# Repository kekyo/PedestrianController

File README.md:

# American pedestrian signal controller on ESP8266

## What's this?

* It's pedestrian signal controller running on ESP8266 (aka ESP-WROOM-02).
* I made custom schematic and artwork from scratch.
  * Use EAGLE 8
* I wrote sequencer code by C++ on ESP8266-Arduino IDE.

### Video

* We record our discussion into YouTube: [Fun with Pedestrian Signal (In japanese)](https://youtu.be/vJiQ18ymqcs)

### NT NAGOYA 2018 conference (2018/10/6)

* We did public and demonstration the MatrixSignalController.
  * It uses with [the ExtremeFeedbackDevice's signal box.](https://github.com/kekyo/ExtremeFeedbackDevice)
  * The three boxes chatting with independent WiFi network, we use http api server and client library.
  * See [the "MatrixSignalController" folder](https://github.com/kekyo/PedestrianController/tree/master/MatrixSignalController) at repository.

## Features

* Basic sequence for american pedestrian signal standard (3 wired control).
* Scheduled time control between signal-on hour and signal-off hour.
* Battery-backuped RTC using scheduler.
* Auto synchronize NTP server with your WiFi AP.

## Schematic and artwork

* I ordered PCB to [Fusion PCB](https://www.seeedstudio.com/fusion_pcb.html) and finished assemble.

## How to assemble PedestrianController

* See also: [How to assemble PedestrianController](HowToAssemble.md)

## License

* Under Apache v2

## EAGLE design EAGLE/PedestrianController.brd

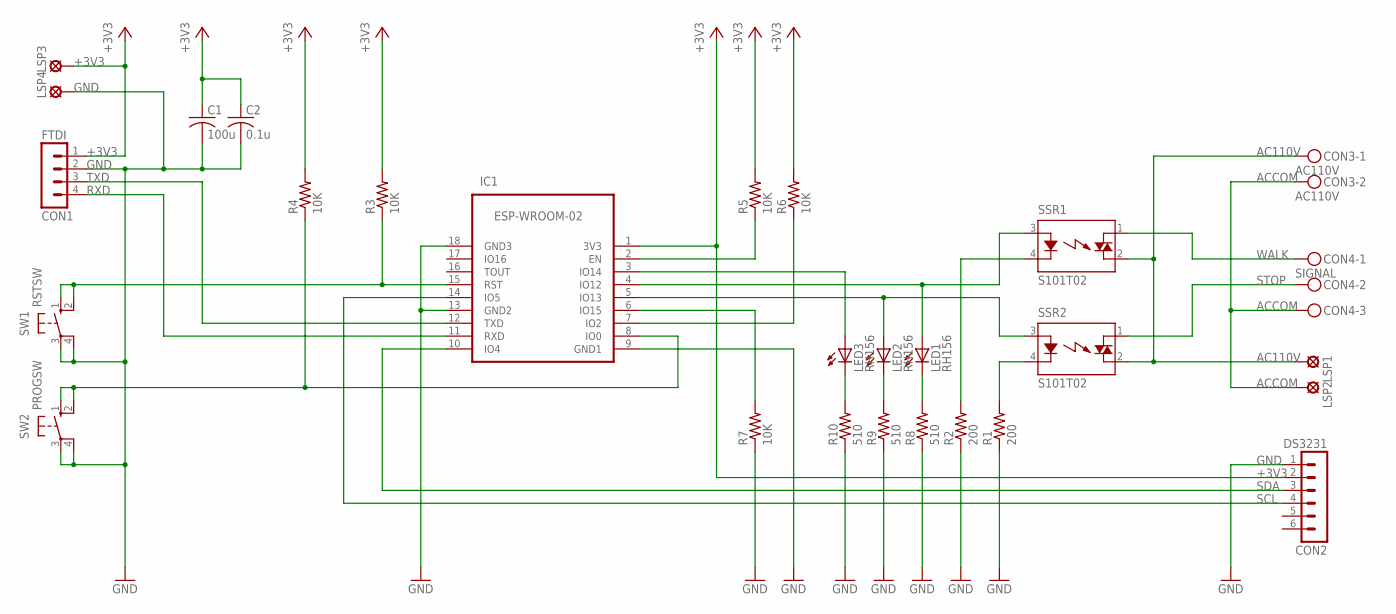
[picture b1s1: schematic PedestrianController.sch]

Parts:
C1: 100u; C050-024X044
C2: 0.1u; C050-024X044
CON1: FTDI; MA04-1
CON2: DS3231; MA06-1
CON3: AC110V; MKDSN1,5/2-5,08
CON4: SIGNAL; MKDSN1,5/3-5,08
IC1: ESP-WROOM-02; FRONT-FACE
LED1, LED2, LED3: RH156; LED3MM
LSP1, LSP2, LSP3, LSP4: LSP10
R1, R2: 200; 0204/7
R3, R4, R5, R6, R7: 10K; 0204/7
R8, R9, R10: 510; 0204/7
SSR1, SSR2: S101T02; S102T0X
SW1: RSTSW; B3F-10XX
SW2: PROGSW; B3F-10XX

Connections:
+3V3: C1.1, C2.1, CON1.1, CON2.2, IC1.1 (3V3), LSP3.MP, R3.2, R4.2, R5.2, R6.2
AC110V: CON3.1, LSP1.MP, SSR1.2 (DS2), SSR2.2 (DS2)
ACCOM: CON3.2, CON4.3, LSP2.MP
GND: C1.2, C2.2, CON1.2, CON2.1, IC1.9 (GND1), IC1.13 (GND2), IC1.18 (GND3), LSP4.MP, R1.1, R2.1, R7.1, R8.1, R9.1, R10.1, SW1.3, SW1.4 (P1), SW2.3, SW2.4 (P1)
unnamed: IC1.8 (IO0), R4.1, SW2.1 (S), SW2.2 (S1)
unnamed: IC1.5 (IO13), LED2.A, SSR2.3 (A)
unnamed: R2.2, SSR1.4 (K)
unnamed: R1.2, SSR2.4 (K)
unnamed: LED1.K (C), R8.2
unnamed: LED2.K (C), R9.2
unnamed: IC1.3 (IO14), LED3.A
unnamed: IC1.4 (IO12), LED1.A, SSR1.3 (A)
unnamed: IC1.15 (RST), R3.1, SW1.1 (S), SW1.2 (S1)
unnamed: LED3.K (C), R10.2
unnamed: IC1.2 (EN), R5.1
unnamed: IC1.7 (IO2), R6.1
unnamed: IC1.6 (IO15), R7.2
RXD: CON1.4, IC1.11 (RXD)
SCL: CON2.4, IC1.14 (IO5)
SDA: CON2.3, IC1.10 (IO4)
STOP: CON4.2, SSR2.1 (DS1)
TXD: CON1.3, IC1.12 (TXD)
WALK: CON4.1, SSR1.1 (DS1)

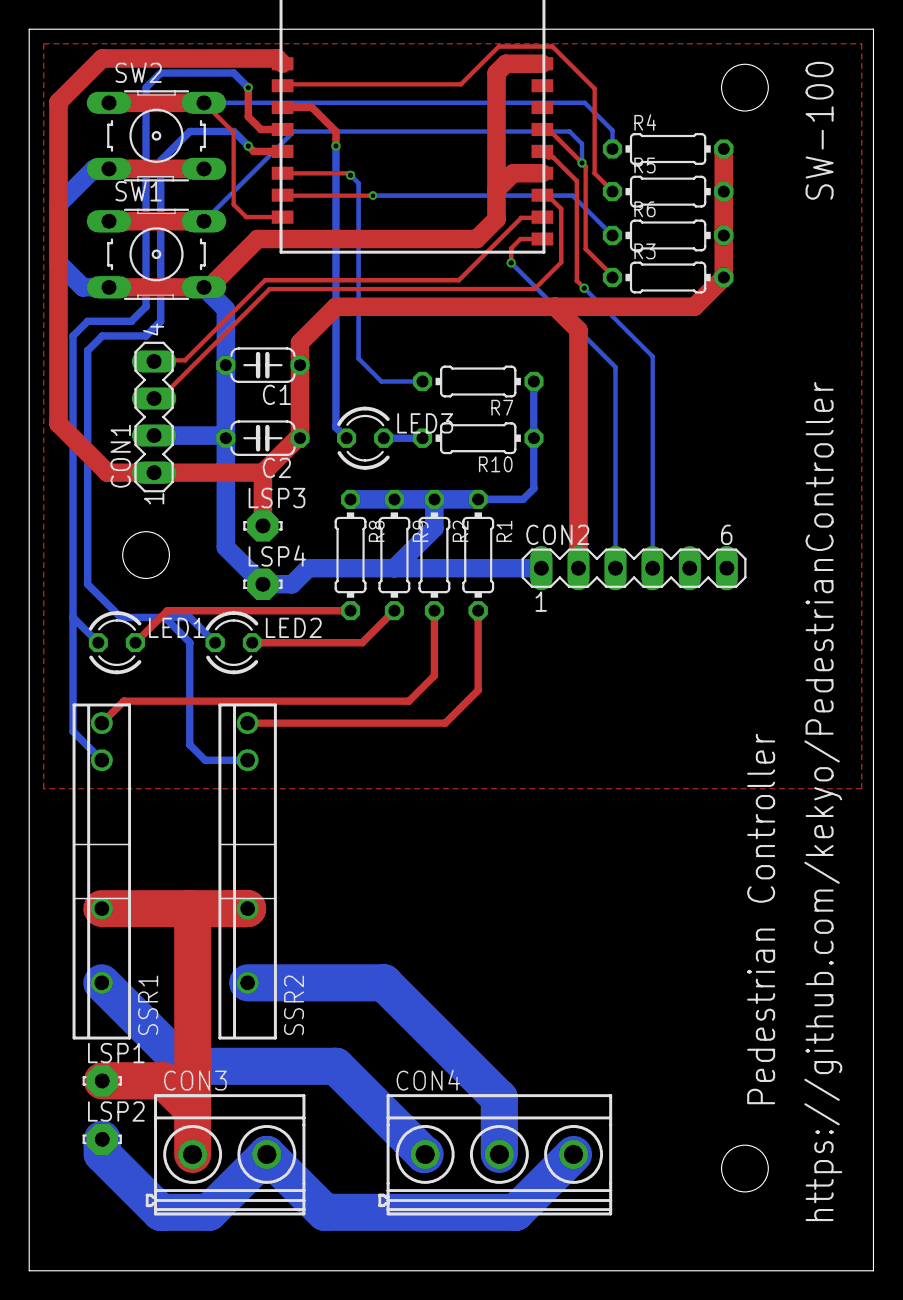
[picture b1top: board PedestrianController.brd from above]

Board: 2 copper layers, 57.8 x 85.0 mm, 28 parts (0 on the bottom side), 23 nets.

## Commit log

2018-04-17 First functional version.
2018-04-17 Fixed invalid year writes to RTC.
2018-04-17 Fixed cut off procedure for WiFi power.
2018-04-17 Add sleep delay.
2018-04-17 Changed NTP server default timezone.
2018-04-17 Fixed not calculates local time.
2018-04-17 Add debug message if enter idling.
2018-04-18 Add EAGLE project folder.
    Add EAGLE projects.
2018-04-18 Finished schematics.
2018-04-18 Placed parts into board.
2018-04-18 Rearranged.
2018-04-18 Rearranged parts.
2018-04-18 Rerouted with broad rule.
2018-04-18 Fixed configuration
2018-04-18 Rearrange parts, add leds.
2018-04-18 Fixed timing for updating RTC.
2018-04-18 Typo
2018-04-19 Add status LEDs.
    * Improvement
2018-04-19 Rearrange wires.
2018-04-19 Add ground pattern.
2018-04-20 First ordered PCB data.
2018-04-20 Add images.
2018-04-20 Bit changed.
2018-04-21 Adjust resistor values by GPIO current specs.
2018-04-22 Changed LED blink sequence.
2018-04-22 Output wifi status.
2018-04-22 Improved wifi status.
2018-04-22 Calculate sleeping time.
2018-04-22 Fixed calculating next time.
2018-05-12 Add images
2018-05-12 Add assembly document.
2018-10-04 Beginning matrix controller demo code (WIP)
2018-10-04 Bark cuckoo.
2018-10-08 Retry fetching current time from ntp server if first time approach.
2018-10-13 Support demo mode (show at NT NAGOYA 2018)
2018-10-15 Update readme.
